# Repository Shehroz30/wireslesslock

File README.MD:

# Wireless bike lock

An ESP32-S3 hosts a web page over WiFi; the Open control energizes a latching solenoid in a
padlock body. The page also reports accelerometer and GPS readings.

The design covers two parts: the control PCB and the padlock. The rest is an existing bike
lock frame.

## How it works

An ESP32-S3 hosts a web page over WiFi; the Open control energizes a latching solenoid in a
padlock body. The page also reports accelerometer and GPS readings.

Interconnect sheet (parts, wiring diagram, wire schedule, open items):

Source (styled, printable): [connect.html](connect.html)

Mechanical design (enclosure and padlock body) is in Onshape:
<https://cad.onshape.com/documents/6c2c18833c9d8444570c43c7/w/6a4bb112d0b0db7159f785b0/e/d206a90808809049c3ae2997?renderMode=0&uiState=6a67dae82bed96ba51b4ef59>

PCB in enclosure:

Padlock with latching solenoid:

## Board specification

| | |
|---|---|
| Dimensions | 50 × 50 mm |
| Stackup | 4 layer (F.Cu / In1.Cu / In2.Cu / B.Cu), 1.6 mm |
| MCU | ESP32-S3-WROOM-1 (WiFi + BLE) |
| Power in | USB-C 5 V, single-cell Li-ion via JST-PH |
| Rails | 3.3 V system (buck-boost), 12 V solenoid (boost) |
| Sensors | LIS2DH12 accelerometer (SPI), SIM68M GNSS + SMD antenna (UART) |
| EDA | KiCad 10.0 |
| Placements | 67 across 44 BOM lines |

## Circuit description

### Power tree

```
USB-C (J1, 5V) ──> U1 BQ24040 ──> Li-ion cell (J2)
                   charge mgmt         │
                                       ├──> U3 TPS63020 buck-boost ──> +3.3V  (MCU, GPS, accel)
                                       │                                 │
                                       └── R7 10k pullup -> U3 EN        └──> U4 TPS55340 boost ──> +12V (solenoid)
```

`U1` (BQ24040) takes 5 V from USB-C and charges the cell. `R1` (560 Ω on ISET) sets the
fast-charge current; `D1`/`D2` are its status outputs. `R2`/`R3` are the 5.1 k CC pulldowns
that make a USB-C source supply 5 V, and `U2` (USBLC6-2SC6) clamps ESD on D+/D−.

The 3.3 V rail comes from `U3` (TPS63020), a buck-boost. A Li-ion cell sags from 4.2 V past
3.3 V as it discharges, so a buck-only regulator would brown out the ESP32 before the cell
was empty. Output is set by `R9` (1 M) / `R10` (180 k) around the 0.5 V reference → 3.28 V.
Inductor is `L2` (2.2 µH).

`U4` (TPS55340) boosts 3.3 V to 12 V through `L1` (10 µH) and `D3`, set by `R12` (86.6 k) /
`R13` (10 k) around the 1.229 V reference → ≈11.9 V. It is a separate rail so solenoid inrush
draws from the bulk caps (`C12`/`C14`/`C16`) rather than the MCU supply.

### Solenoid drive

`CTRL_P` (GPIO40) → `R18` (220 Ω gate series) → `Q1` (AO3400A, low-side N-ch FET). `R17`
(10 k) pulls the gate down so the coil is off through boot and reset. `D4` (S1M) is the
flyback diode across the coil. The coil connects to `TP1` (+12 V) and `TP2` (Q1 drain).

There is no hold-current limiting in hardware. The firmware caps coil energization time
instead (`MAX_OPEN_MS`, 5 s). Any other code driving `CTRL_P` must enforce the same limit.

### GPS

`U6` (SIM68M) streams NMEA at 9600 baud on the primary UART. `U8` (GPS1003) is the SMD
antenna, fed through a pi matching network: shunt `C22`, series `R19` (0 Ω), shunt `L4`
(18 nH). The 0 Ω / 0402 placeholders allow the match to be tuned after measurement.

## Pin map (U5, ESP32-S3-WROOM-1)

| Net | GPIO | Connects to |
|---|---|---|
| `CTRL_P` | 40 | Q1 gate (solenoid) via R18 |
| `LI_CS` | 10 | LIS2DH12 chip select |
| `SPI_MOSI` | 11 | LIS2DH12 SDI |
| `SPI_SCK` | 12 | LIS2DH12 SPC |
| `SPI_MISO` | 13 | LIS2DH12 SDO |
| `UART1_RX` | 17 | SIM68M TXD0, primary NMEA out |
| `UART1_TX` | 18 | SIM68M RXD0 |
| `UART0_RX` / `UART0_TX` | 6 / 7 | SIM68M secondary/debug UART |
| `BOOT` | 0 | SW3 tactile |
| `RST` | EN | SW2 tactile (R16 10 k pullup) |
| `TM` | — | Q2 → status LED D5; unused by the current firmware |

The accelerometer runs SPI mode 3 at 1 MHz. Its INT1/INT2 pins are not connected, so motion
detection is by polling.

## Firmware

The sketch is `firmware/wireslesslock_controller/wireslesslock_controller.ino`. It joins a
WiFi network, serves a page on port 80, and polls `/data` once a second for accelerometer and
GPS values. There is no cloud service or backend; the lock is reachable only on the local
network.

| Route | Method | Function |
|---|---|---|
| `/` | GET | Control page |
| `/data` | GET | JSON: `locked`, `accel.x/y/z` (g), `gps.fix/sats/lat/lon` |
| `/open` | POST | Energize solenoid (auto-releases after 5 s) |
| `/close` | POST | De-energize |

### Flashing

1. Arduino IDE → Boards Manager → install the esp32 package.
2. Library Manager → install TinyGPSPlus (Mikal Hart). The remaining dependencies are part of
   the ESP32 core.
3. Set `WIFI_SSID` / `WIFI_PASS` at the top of the sketch.
4. Connect over USB, select the board and port under Tools, and upload.

If upload stalls at `Connecting...`: hold BOOT (SW3), tap RESET (SW2), release BOOT. After
"Done uploading" the sketch is running; the serial monitor at 115200 baud prints the assigned
IP address.

## Fabrication

`gerbers.zip` is the fab package: 4 layer, 1.6 mm, 50 × 50 mm.

For assembly, `production/` holds `bom.csv`, `positions.csv`, `designators.csv`, and
`netlist.ipc`. These are generated by the KiCad Fabrication Toolkit plugin (settings in
`fabrication-toolkit-options.json`); regenerate them with the plugin rather than editing the
CSVs directly.

All parts are LCSC/JLCPCB-orderable except the solenoid and the battery, which are selected to
fit the padlock body.

## Bill of materials

67 placements, 44 lines. Machine-readable copy with purchase links: [BOM.csv](BOM.csv).
`production/bom.csv` is the plugin-generated file and is the reference for designators and
values; the table below adds the function of each part.

| Designator | Qty | Value | Footprint | Function | LCSC |
|---|---|---|---|---|---|
| `C1, C2` | 2 | 1uf | 0603 | USB VBUS / charger input bulk decoupling (U1 BQ24040 IN, OUT) | [C15849](https://www.lcsc.com/search?q=C15849) |
| `C10` | 1 | 100nF | 0402 | ESP32-S3 (U5) supply decoupling | [C1525](https://www.lcsc.com/search?q=C1525) |
| `C11, C19, C21, C7` | 4 | 0.1uF | 0603 | General IC decoupling (U4 VIN/VCC, GPS, accel) | [C14663](https://www.lcsc.com/search?q=C14663) |
| `C12, C14, C16, C5` | 4 | 4.7uF | 1206 | 12V solenoid rail bulk output caps (U4 boost output) | [C29823](https://www.lcsc.com/search?q=C29823) |
| `C13, C15, C17` | 3 | 22uf | 0805 | 3.3V rail bulk output caps (U3 buck-boost output) | [C45783](https://www.lcsc.com/search?q=C45783) |
| `C18, C26, C27, C3, C8` | 5 | 100nF | 0603 | Local HF decoupling, 3.3V rail | [C14663](https://www.lcsc.com/search?q=C14663) |
| `C20` | 1 | 22uF | 1206 | 3.3V bulk reservoir for RF/GPS current bursts | [C12891](https://www.lcsc.com/search?q=C12891) |
| `C22, R19` | 2 | 0 | 0402 | GPS antenna pi-match: shunt cap + series 0R (U8 -> U6 GNSS_ANT) | [C1952](https://www.lcsc.com/search?q=C1952) |
| `C23` | 1 | 4.7uF | 0402 | 3.3V decoupling, SIM68M GPS module (U6) | [C23733](https://www.lcsc.com/search?q=C23733) |
| `C28, C4, C6` | 3 | 10uF | 0603 | Mid-value decoupling, battery and 3.3V rails | [C19702](https://www.lcsc.com/search?q=C19702) |
| `C9` | 1 | 0.047uF | 0603 | TPS55340 (U4) soft-start cap on SS pin | [C1622](https://www.lcsc.com/search?q=C1622) |
| `D1, D2, D5` | 3 | LED | 0603 | Status LEDs: D1/D2 = BQ24040 CHG/PGOOD, D5 = MCU-driven (via Q2) | [C2290](https://www.lcsc.com/search?q=C2290) |
| `D3` | 1 | D_Schottky | SMA_L4.3-W2.7-LS5.1-RD | Boost rectifier for U4 (SW node -> +12V) | [C8678](https://www.lcsc.com/search?q=C8678) |
| `D4` | 1 | S1M | SMA_L4.3-W2.7-LS5.1-RD | Flyback/freewheel diode across the solenoid coil | [C51898151](https://www.lcsc.com/search?q=C51898151) |
| `J1` | 1 | MC-311D | USB-C-SMD_MC-311D | USB-C receptacle: 5V charge input + native USB D+/D- | [C136423](https://www.lcsc.com/search?q=C136423) |
| `J2` | 1 | BATTERY | CONN-TH_S2B-PH-K-S-GW | JST-PH 2-pin Li-ion battery connector | [C157932](https://www.lcsc.com/search?q=C157932) |
| `L1` | 1 | 10uH | IND-SMD_L7.2-W6.6_GPSR07X0 | 10uH boost inductor for U4 (+3.3V -> +12V) | [C5189958](https://www.lcsc.com/search?q=C5189958) |
| `L2` | 1 | 2.2uH | L1008 | 2.2uH buck-boost inductor for U3 (TPS63020 L1/L2 pins) | [C86092](https://www.lcsc.com/search?q=C86092) |
| `L4` | 1 | 18nH | 0402 | 18nH shunt inductor, GPS antenna matching network | [C86060](https://www.lcsc.com/search?q=C86060) |
| `Q1` | 1 | AO3400A | SOT-23 | N-ch FET, low-side solenoid driver (gate = CTRL_P / GPIO40) | [C20917](https://www.lcsc.com/search?q=C20917) |
| `Q2` | 1 | DTC143Z | SOT-323_SC-70 | Digital NPN (built-in bias) driving status LED D5 from net TM | [C53066](https://www.lcsc.com/search?q=C53066) |
| `R1` | 1 | 560 | 0603 | BQ24040 ISET: sets fast-charge current | [C23204](https://www.lcsc.com/search?q=C23204) |
| `R10` | 1 | 180k | 0603 | U3 (TPS63020) feedback divider, bottom leg -> 3.3V out | [C22827](https://www.lcsc.com/search?q=C22827) |
| `R11` | 1 | 75k | 0603 | U4 (TPS55340) FREQ pin: switching frequency set | [C23242](https://www.lcsc.com/search?q=C23242) |
| `R12` | 1 | 86.6K | 0603 | U4 feedback divider, top leg from +12V | [C23121](https://www.lcsc.com/search?q=C23121) |
| `R13, R16, R7` | 3 | 10k | 0603 | R13 = U4 FB bottom leg (12V), R16 = RST pullup, R7 = U3 EN pullup | [C25804](https://www.lcsc.com/search?q=C25804) |
| `R17` | 1 | 10k | 0402 | Gate pulldown on CTRL_P (holds solenoid off during boot/reset) | [C60489](https://www.lcsc.com/search?q=C60489) |
| `R18` | 1 | 220 | 0402 | Gate series resistor for Q1 | [C25091](https://www.lcsc.com/search?q=C25091) |
| `R2, R3` | 2 | 5.1k | 0402 | USB-C CC1/CC2 5.1k pulldowns (advertise 5V sink) | [C25905](https://www.lcsc.com/search?q=C25905) |
| `R20` | 1 | 1k | 0402 | Series resistor for status LED D5 | [C11702](https://www.lcsc.com/search?q=C11702) |
| `R4, R5` | 2 | 1k | 0603 | Series resistors for charge-status LEDs D1/D2 | [C21190](https://www.lcsc.com/search?q=C21190) |
| `R8` | 1 | 2k | 0603 | U4 COMP network resistor (loop compensation) | [C22975](https://www.lcsc.com/search?q=C22975) |
| `R9` | 1 | 1M | 0603 | U3 feedback divider, top leg from 3.3V out | [C22935](https://www.lcsc.com/search?q=C22935) |
| `SW2, SW3` | 2 | TS-1088-AR02016 | SW-SMD_L3.9-W3.0-P4.45 | Tactile switches: SW2 = RESET (EN), SW3 = BOOT (IO0) | [C720477](https://www.lcsc.com/search?q=C720477) |
| `TP1` | 1 | VCC_SOL | TestPoint_Loop_D3.80mm_Drill2.8mm | Test point / solenoid output: +12V | — |
| `TP2` | 1 | GND_SOL | TestPoint_Loop_D3.80mm_Drill2.8mm | Test point / solenoid output: switched low side (Q1 drain) | — |
| `U1` | 1 | BQ24040DSQR | WSON-10_L2.0-W2.0-P0.40-BL-EP | Li-ion linear charge management IC (USB 5V -> battery) | [C81080](https://www.lcsc.com/search?q=C81080) |
| `U2` | 1 | USBLC6-2SC6 | SOT-23-6 | USB D+/D- ESD protection array | [C2827654](https://www.lcsc.com/search?q=C2827654) |
| `U3` | 1 | TPS63020DSJR | VSON-14_L4.0-W3.0-P0.50-BL-EP_TI_DSJ | Buck-boost converter: battery (2.5-5.5V) -> 3.3V system rail | [C15483](https://www.lcsc.com/search?q=C15483) |
| `U4` | 1 | TPS55340RTER | VQFN-16_L3.0-W3.0-P0.50-BL-EP1.7 | Boost converter: 3.3V -> 12V solenoid rail | [C169167](https://www.lcsc.com/search?q=C169167) |
| `U5` | 1 | ESP32-S3-WROOM-1 | ESP32-S3-WROOM-1 | Main MCU/radio: ESP32-S3, WiFi + BLE, hosts the control page | [C2913202](https://www.lcsc.com/search?q=C2913202) |
| `U6` | 1 | SIM68M | GPSM-SMD_18P-L10.1-W9.7-P1.10 | GNSS receiver module, NMEA out over UART at 9600 baud | [C2999762](https://www.lcsc.com/search?q=C2999762) |
| `U7` | 1 | LIS2DH12TR | LGA-12_L2.0-W2.0-P0.50-BL | 3-axis accelerometer (SPI) - tamper / motion detection | [C110926](https://www.lcsc.com/search?q=C110926) |
| `U8` | 1 | GPS1003 | ANT-SMD_L10.0-W3.0 | SMD GPS patch antenna, 1575.42 MHz | [C239243](https://www.lcsc.com/search?q=C239243) |

Not on the BOM, selected to fit the padlock:

| Item | Notes |
|---|---|
| Latching solenoid | Driven from TP1/TP2 at 12 V, low-side switched |
| Li-ion cell | Single cell, JST-PH 2-pin to J2 |

## Repository layout

```
wireslesslock.kicad_pro      project file
wireslesslock.kicad_sch      root schematic (MCU, GPS, accel, switches)
power.kicad_sch              "Power" sub-sheet (charging, both converters, USB-C)
wireslesslock.kicad_pcb      4-layer board layout
easyeda2kicad.*              project-local library: parts converted from LCSC/EasyEDA
                             (BQ24040, TPS63020, TPS55340, GPS antenna, WSON/VSON pkgs)
BOM.csv                      annotated BOM (this README's table)
production/                  generated fab outputs (plugin output, not source)
gerbers.zip                  fab package
firmware/                    ESP32-S3 Arduino sketch
3dfiles/                     STEP export + padlock mechanism snapshots from Onshape
docs/                        README images
archive/                     timestamped project backups
```

## Verifying changes

There is no build or test command. Changes are verified by opening the project in KiCad and
running ERC on the schematic and DRC on the board.

## License

[MIT](LICENSE).

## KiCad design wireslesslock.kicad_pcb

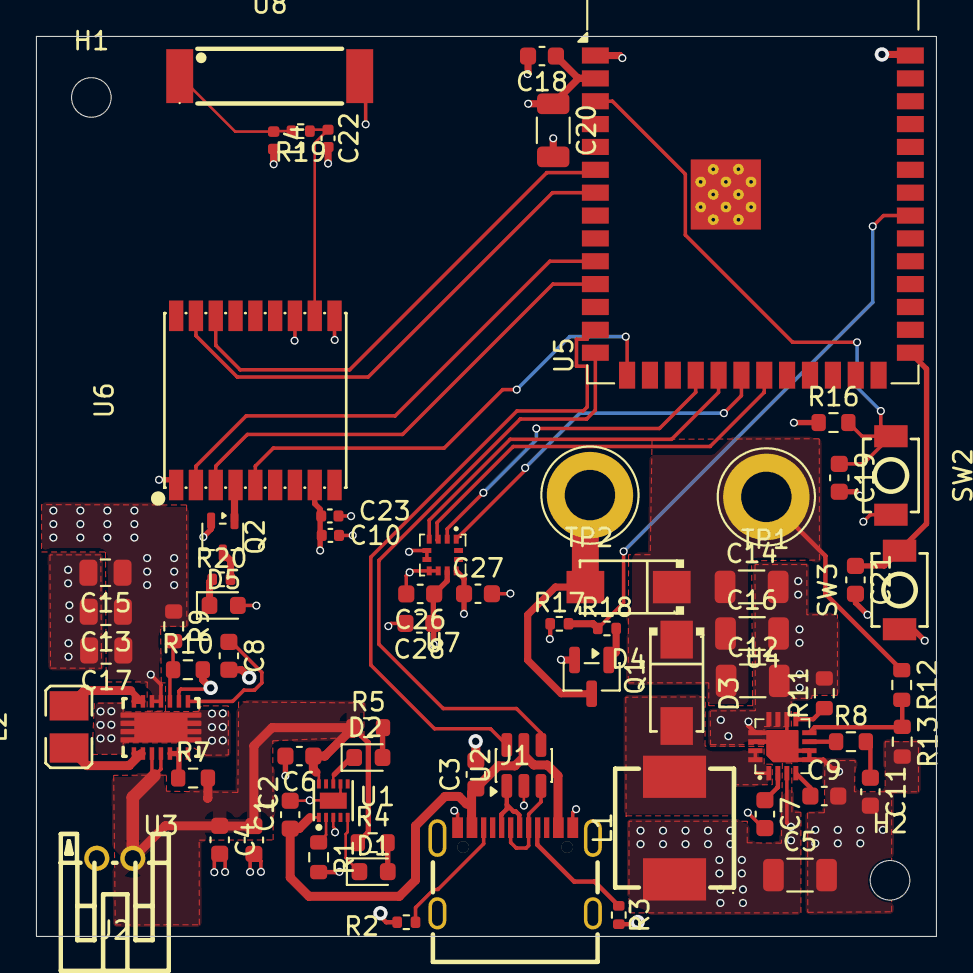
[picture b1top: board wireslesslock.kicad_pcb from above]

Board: 4 copper layers, 50.0 x 50.0 mm, 69 parts (0 on the bottom side), 47 nets.

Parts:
C1, C2: 1uf; C_0603_1608Metric
C3, C18, C26, C27: 100nF; C_0603_1608Metric
C4, C6: 10uf; C_0603_1608Metric
C5, C12, C14, C16: 4.7uF; C_1206_3216Metric
C7, C11, C19, C21: 0.1uF; C_0603_1608Metric
C8: 100nf; C_0603_1608Metric
C9: 0.047uF; C_0603_1608Metric
C10: 100nF; C_0402_1005Metric
C13, C15, C17: 22uf; C_0805_2012Metric
C20: 22uF; C_1206_3216Metric
C22: 0; C_0402_1005Metric
C23: 4.7uF; C_0402_1005Metric
C28: 10uF; C_0603_1608Metric
D1, D2, D5: LED; LED_0603_1608Metric
D3: D_Schottky; SMA_L4.3-W2.7-LS5.1-RD
D4: S1M; SMA_L4.3-W2.7-LS5.1-RD
H1, H2: MountingHole; MountingHole_2.2mm_M2
J1: MC-311D; USB-C-SMD_MC-311D
J2: BATTERY; CONN-TH_S2B-PH-K-S-GW
L1: 10uH; IND-SMD_L7.2-W6.6_GPSR07X0
L2: 2.2uH; L1008
L4: 18nH; L_0402_1005Metric
Q1: AO3400A; SOT-23
Q2: DTC143Z; SOT-323_SC-70
R1: 560; R_0603_1608Metric
R2, R3: 5.1k; R_0402_1005Metric
R4, R5: 1k; R_0603_1608Metric
R7, R13, R16: 10k; R_0603_1608Metric
R8: 2k; R_0603_1608Metric
R9: 1M; R_0603_1608Metric
R10: 180k; R_0603_1608Metric
R11: 75k; R_0603_1608Metric
R12: 86.6K; R_0603_1608Metric
R17: 10k; R_0402_1005Metric
R18: 220; R_0402_1005Metric
R19: 0; R_0402_1005Metric
R20: 1k; R_0402_1005Metric
SW2, SW3: TS-1088-AR02016; SW-SMD_L3.9-W3.0-P4.45
TP1: VCC_SOL; TestPoint_Loop_D3.80mm_Drill2.8mm
TP2: GND_SOL; TestPoint_Loop_D3.80mm_Drill2.8mm
U1: BQ24040DSQR; WSON-10_L2.0-W2.0-P0.40-BL-EP
U2: USBLC6-2SC6; SOT-23-6
U3: TPS63020DSJR; VSON-14_L4.0-W3.0-P0.50-BL-EP_TI_DSJ
U4: TPS55340RTER; VQFN-16_L3.0-W3.0-P0.50-BL-EP1.7
U5: ESP32-S3-WROOM-1
U6: SIM68M; GPSM-SMD_18P-L10.1-W9.7-P1.10
U7: LIS2DH12TR; LGA-12_L2.0-W2.0-P0.50-BL
U8: GPS1003; ANT-SMD_L10.0-W3.0

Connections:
+3.3V: C5.1, C10.1, C13.1, C15.1, C17.1, C18.1, C20.1, C23.1, C26.1, C27.1, C28.1, D5.2 (A), L1.1, R9.1, R16.1, U3.4 (VOUT), U3.5 (VOUT), U4.3 (EN), U5.2 (3V3), U6.8 (VCC), U7.9 (VDD), U7.10 (VDD_IO)
+5V: C1.1, C3.1, J1.A4-B9 (VBUS), J1.B4-A9 (VBUS), U1.1 (IN), U2.5 (VBUS)
+12V: C12.1, C14.1, C16.1, D3.1 (K), D4.1 (K), R12.1, TP1.1 (1_1)
/wireslesslock/BOOT: C21.1, SW3.2, U5.27 (IO0)
/wireslesslock/CTRL_P: R17.2, R18.1, U5.33 (IO40)
/wireslesslock/LI_CS: U5.18 (IO10), U7.2 (CS)
/wireslesslock/RST: C19.1, R16.2, SW2.1, U5.3 (EN)
/wireslesslock/SIM_INT: U5.15 (IO3), U6.5 (EXTINT)
/wireslesslock/SPI_MISO: U5.21 (IO13), U7.3 (SDO/SA0)
/wireslesslock/SPI_MOSI: U5.19 (IO11), U7.4 (SDA/SDI/SDO)
/wireslesslock/SPI_SCK: U5.20 (IO12), U7.1 (SCL/SPC)
/wireslesslock/TM: Q2.1 (B), U6.4 (TIMEMARK)
/wireslesslock/UART0_RX: U5.6 (IO6), U6.16 (TXD1/SDA)
/wireslesslock/UART0_TX: U5.7 (IO7), U6.17 (RXD1/SCL)
/wireslesslock/UART1_RX: U5.10 (IO17), U6.2 (TXD0)
/wireslesslock/UART1_TX: U5.11 (IO18), U6.3 (RXD0)
D+: U2.4 (I/O2), U5.14 (USB_D+)
D-: U2.6 (I/O1), U5.13 (USB_D-)
GND: C1.2, C2.2, C3.2, C4.2, C5.2, C6.2, C7.2, C8.2, C9.2, C10.2, C11.2, C12.2, C13.2, C14.2, C15.2, C16.2, C17.2, C18.2, C19.2, C20.2, C21.2, C22.2, C23.2, C26.2, C27.2, C28.2, J1.A1-B12 (GND), J1.B1-A12 (GND), J2.1, L4.2, Q1.2 (S), Q2.2 (E), R1.2, R2.2, R3.2, R10.2, R11.2, R13.2, R17.1, SW2.2, SW3.1, U1.3 (VSS), U1.7 (ISET2), U1.11 (EP), U2.2 (GND), U3.2 (GND), U3.15 (PGND), U4.5 (SYNC), U4.6 (AGND), U4.10 (NC), U4.11 (PGND), U4.12 (PGND), U4.13 (PGND), U4.14 (NC), U4.17 (EP), U5.1 (GND), U5.40 (GND), U5.41 (GND), U6.1 (GND), U6.10 (GND), U6.12 (GND), U7.5 (RES), U7.6 (GND), U7.7 (GND), U7.8 (GND), U8.2
unnamed: C11.1, R8.2
unnamed: D1.2 (A), R4.2
unnamed: D1.1 (K), U1.5 (~PG)
unnamed: D2.2 (A), R5.2
unnamed: D2.1 (K), U1.8 (~CHG)
unnamed: D3.2 (A), L1.2, U4.1 (SW), U4.15 (SW), U4.16 (SW)
unnamed: D4.2 (A), Q1.3 (D), TP2.1 (1_1)
unnamed: D5.1 (K), R20.1
unnamed: J1.A7 (DN1), J1.B7 (DN2), U2.1 (I/O1)
unnamed: J1.A6 (DP1), J1.B6 (DP2), U2.3 (I/O2)
unnamed: J1.A8 (SBU1), R3.1
unnamed: J1.B8 (SBU2), R2.1
unnamed: C2.1, C4.1, C6.1, J2.2, R4.1, R5.1, R7.2, U1.10 (OUT), U3.10 (VIN), U3.11 (VIN)
unnamed: L2.1, U3.8 (L1), U3.9 (L1)
unnamed: L2.2, U3.6 (L2), U3.7 (L2)
unnamed: L4.1, R19.2, U8.1
unnamed: Q1.1 (G), R18.2
unnamed: Q2.3 (C), R20.2
unnamed: R1.1, U1.2 (ISET)
unnamed: R7.1, U3.12 (EN), U3.13 (PS/SYNC)
unnamed: R9.2, R10.1, U3.3 (FB)
unnamed: C8.1, U3.1 (VINA)
unnamed: R8.1, U4.7 (COMP)
unnamed: R12.2, R13.1, U4.8 (FB)
unnamed: R11.1, U4.9 (FREQ)
unnamed: C9.1, U4.4 (SS)
unnamed: C7.1, U4.2 (VIN)
unnamed: C22.1, R19.1, U6.11 (GNSS_ANT)

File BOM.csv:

Designator,Qty,Value,Footprint,Function,LCSC Part #,Purchase Link
"C1, C2",2,1uf,0603,"USB VBUS / charger input bulk decoupling (U1 BQ24040 IN, OUT)",C15849,https://www.lcsc.com/search?q=C15849
C10,1,100nF,0402,ESP32-S3 (U5) supply decoupling,C1525,https://www.lcsc.com/search?q=C1525
"C11, C19, C21, C7",4,0.1uF,0603,"General IC decoupling (U4 VIN/VCC, GPS, accel)",C14663,https://www.lcsc.com/search?q=C14663
"C12, C14, C16, C5",4,4.7uF,1206,12V solenoid rail bulk output caps (U4 boost output),C29823,https://www.lcsc.com/search?q=C29823
"C13, C15, C17",3,22uf,0805,3.3V rail bulk output caps (U3 buck-boost output),C45783,https://www.lcsc.com/search?q=C45783
"C18, C26, C27, C3, C8",5,100nF,0603,"Local HF decoupling, 3.3V rail",C14663,https://www.lcsc.com/search?q=C14663
C20,1,22uF,1206,3.3V bulk reservoir for RF/GPS current bursts,C12891,https://www.lcsc.com/search?q=C12891
"C22, R19",2,0,0402,GPS antenna pi-match: shunt cap + series 0R (U8 -> U6 GNSS_ANT),C1952,https://www.lcsc.com/search?q=C1952
C23,1,4.7uF,0402,"3.3V decoupling, SIM68M GPS module (U6)",C23733,https://www.lcsc.com/search?q=C23733
"C28, C4, C6",3,10uF,0603,"Mid-value decoupling, battery and 3.3V rails",C19702,https://www.lcsc.com/search?q=C19702
C9,1,0.047uF,0603,TPS55340 (U4) soft-start cap on SS pin,C1622,https://www.lcsc.com/search?q=C1622
"D1, D2, D5",3,LED,0603,"Status LEDs: D1/D2 = BQ24040 CHG/PGOOD, D5 = MCU-driven (via Q2)",C2290,https://www.lcsc.com/search?q=C2290
D3,1,D_Schottky,SMA_L4.3-W2.7-LS5.1-RD,Boost rectifier for U4 (SW node -> +12V),C8678,https://www.lcsc.com/search?q=C8678
D4,1,S1M,SMA_L4.3-W2.7-LS5.1-RD,Flyback/freewheel diode across the solenoid coil,C51898151,https://www.lcsc.com/search?q=C51898151
J1,1,MC-311D,USB-C-SMD_MC-311D,USB-C receptacle: 5V charge input + native USB D+/D-,C136423,https://www.lcsc.com/search?q=C136423
J2,1,BATTERY,CONN-TH_S2B-PH-K-S-GW,JST-PH 2-pin Li-ion battery connector,C157932,https://www.lcsc.com/search?q=C157932
L1,1,10uH,IND-SMD_L7.2-W6.6_GPSR07X0,10uH boost inductor for U4 (+3.3V -> +12V),C5189958,https://www.lcsc.com/search?q=C5189958
L2,1,2.2uH,L1008,2.2uH buck-boost inductor for U3 (TPS63020 L1/L2 pins),C86092,https://www.lcsc.com/search?q=C86092
L4,1,18nH,0402,"18nH shunt inductor, GPS antenna matching network",C86060,https://www.lcsc.com/search?q=C86060
Q1,1,AO3400A,SOT-23,"N-ch FET, low-side solenoid driver (gate = CTRL_P / GPIO40)",C20917,https://www.lcsc.com/search?q=C20917
Q2,1,DTC143Z,SOT-323_SC-70,Digital NPN (built-in bias) driving status LED D5 from net TM,C53066,https://www.lcsc.com/search?q=C53066
R1,1,560,0603,BQ24040 ISET: sets fast-charge current,C23204,https://www.lcsc.com/search?q=C23204
R10,1,180k,0603,"U3 (TPS63020) feedback divider, bottom leg -> 3.3V out",C22827,https://www.lcsc.com/search?q=C22827
R11,1,75k,0603,U4 (TPS55340) FREQ pin: switching frequency set,C23242,https://www.lcsc.com/search?q=C23242
R12,1,86.6K,0603,"U4 feedback divider, top leg from +12V",C23121,https://www.lcsc.com/search?q=C23121
"R13, R16, R7",3,10k,0603,"R13 = U4 FB bottom leg (12V), R16 = RST pullup, R7 = U3 EN pullup",C25804,https://www.lcsc.com/search?q=C25804
R17,1,10k,0402,Gate pulldown on CTRL_P (holds solenoid off during boot/reset),C60489,https://www.lcsc.com/search?q=C60489
R18,1,220,0402,Gate series resistor for Q1,C25091,https://www.lcsc.com/search?q=C25091
"R2, R3",2,5.1k,0402,USB-C CC1/CC2 5.1k pulldowns (advertise 5V sink),C25905,https://www.lcsc.com/search?q=C25905
R20,1,1k,0402,Series resistor for status LED D5,C11702,https://www.lcsc.com/search?q=C11702
"R4, R5",2,1k,0603,Series resistors for charge-status LEDs D1/D2,C21190,https://www.lcsc.com/search?q=C21190
R8,1,2k,0603,U4 COMP network resistor (loop compensation),C22975,https://www.lcsc.com/search?q=C22975
R9,1,1M,0603,"U3 feedback divider, top leg from 3.3V out",C22935,https://www.lcsc.com/search?q=C22935
"SW2, SW3",2,TS-1088-AR02016,SW-SMD_L3.9-W3.0-P4.45,"Tactile switches: SW2 = RESET (EN), SW3 = BOOT (IO0)",C720477,https://www.lcsc.com/search?q=C720477
TP1,1,VCC_SOL,TestPoint_Loop_D3.80mm_Drill2.8mm,Test point / solenoid output: +12V,,
TP2,1,GND_SOL,TestPoint_Loop_D3.80mm_Drill2.8mm,Test point / solenoid output: switched low side (Q1 drain),,
U1,1,BQ24040DSQR,WSON-10_L2.0-W2.0-P0.40-BL-EP,Li-ion linear charge management IC (USB 5V -> battery),C81080,https://www.lcsc.com/search?q=C81080
U2,1,USBLC6-2SC6,SOT-23-6,USB D+/D- ESD protection array,C2827654,https://www.lcsc.com/search?q=C2827654
U3,1,TPS63020DSJR,VSON-14_L4.0-W3.0-P0.50-BL-EP_TI_DSJ,Buck-boost converter: battery (2.5-5.5V) -> 3.3V system rail,C15483,https://www.lcsc.com/search?q=C15483
U4,1,TPS55340RTER,VQFN-16_L3.0-W3.0-P0.50-BL-EP1.7,Boost converter: 3.3V -> 12V solenoid rail,C169167,https://www.lcsc.com/search?q=C169167
U5,1,ESP32-S3-WROOM-1,ESP32-S3-WROOM-1,"Main MCU/radio: ESP32-S3, WiFi + BLE, hosts the control page",C2913202,https://www.lcsc.com/search?q=C2913202
U6,1,SIM68M,GPSM-SMD_18P-L10.1-W9.7-P1.10,"GNSS receiver module, NMEA out over UART at 9600 baud",C2999762,https://www.lcsc.com/search?q=C2999762
U7,1,LIS2DH12TR,LGA-12_L2.0-W2.0-P0.50-BL,3-axis accelerometer (SPI) - tamper / motion detection,C110926,https://www.lcsc.com/search?q=C110926
U8,1,GPS1003,ANT-SMD_L10.0-W3.0,"SMD GPS patch antenna, 1575.42 MHz",C239243,https://www.lcsc.com/search?q=C239243
